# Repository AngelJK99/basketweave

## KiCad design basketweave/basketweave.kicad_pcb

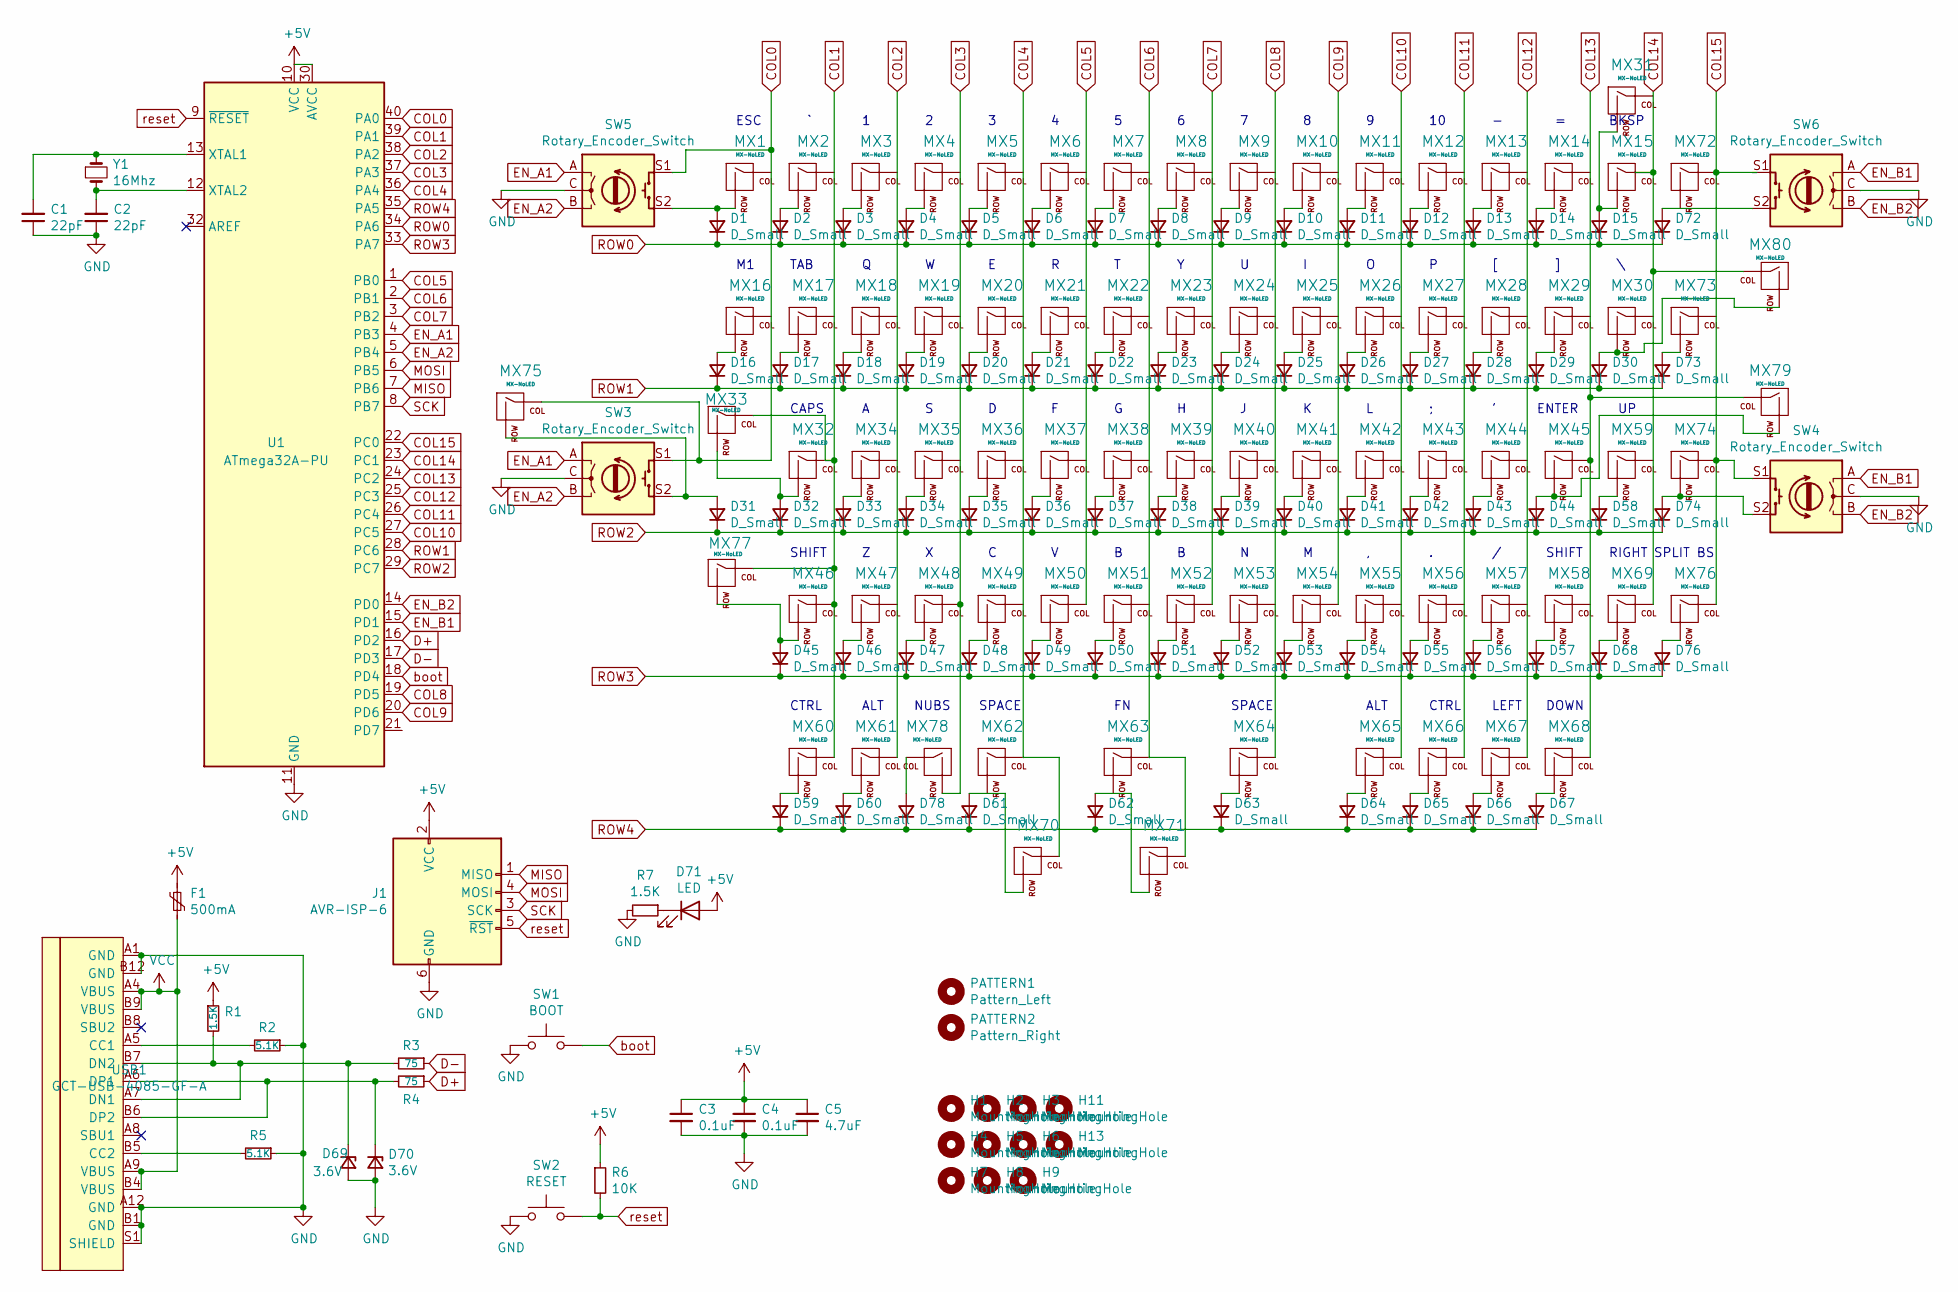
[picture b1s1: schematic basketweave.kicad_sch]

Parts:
C1, C2: 22pF; C_Disc_D3.0mm_W2.0mm_P2.50mm
C3, C4: 0.1uF; C_Disc_D4.3mm_W1.9mm_P5.00mm
C5: 4.7uF; CP_Radial_D4.0mm_P1.50mm
D1, D2, D3, D4, D5, D6, D7, D8, D9, D10, D11, D12, D13, D14, D15, D16, D17, D18, D19, D20, D21, D22, D23, D24, D25, D26, D27, D28, D29, D30, D31, D32, D33, D34, D35, D36, D37, D38, D39, D40, D41, D42, D43, D44, D45, D46, D47, D48, D49, D50, D51, D52, D53, D54, D55, D56, D57, D58, D59, D60, D61, D62, D63, D64, D65, D66, D67, D68, D72, D73, D74, D76, D78: D_Small; D_DO-35_SOD27_P7.62mm_Horizontal
D69, D70: 3.6V; D_DO-35_SOD27_P7.62mm_Horizontal
D71: LED; LED_D3.0mm_Clear
F1: 500mA; polyfuse_5.1mm
H1, H2, H3, H4, H5, H6, H7, H8, H9, H11, H13: MountingHole; MountingHole_2.2mm_M2_Pad
J1: AVR-ISP-6; PinHeader_2x03_P2.54mm_Vertical
MX1, MX2, MX3, MX4, MX5, MX6, MX7, MX8, MX9, MX10, MX11, MX12, MX13, MX14, MX16, MX18, MX19, MX20, MX21, MX22, MX23, MX24, MX25, MX26, MX27, MX28, MX29, MX31, MX34, MX35, MX36, MX37, MX38, MX39, MX40, MX41, MX42, MX43, MX44, MX47, MX48, MX49, MX50, MX51, MX52, MX53, MX54, MX55, MX56, MX57, MX59, MX67, MX68, MX69, MX71, MX72, MX73, MX74, MX75, MX76, MX78, MX80: MX-NoLED; MXOnly-1U-NoLED
MX15: MX-NoLED; MXOnly-2U-NoLED
MX17, MX30, MX60, MX61, MX65, MX66: MX-NoLED; MXOnly-1.5U-NoLED
MX32, MX63, MX77: MX-NoLED; MXOnly-1.25U-NoLED
MX33, MX58: MX-NoLED; MXOnly-1.75U-NoLED
MX45, MX46, MX70: MX-NoLED; MXOnly-2.25U-ReversedStabilizers-NoLED
MX62: MX-NoLED; MXOnly-2U-ReversedStabilizers-NoLED
MX64: MX-NoLED; MXOnly-2.75U-ReversedStabilizers-NoLED
MX79: MX-NoLED; MXOnly-ISO-ROTATED-ReversedStabilizers-NoLED
PATTERN1: Pattern_Left; pattern_left
PATTERN2: Pattern_Right; pattern_right
R1, R7: 1.5K; R_Axial_DIN0204_L3.6mm_D1.6mm_P5.08mm_Horizontal
R2, R5: 5.1K; R_Axial_DIN0204_L3.6mm_D1.6mm_P5.08mm_Horizontal
R3, R4: 75; R_Axial_DIN0204_L3.6mm_D1.6mm_P5.08mm_Horizontal
R6: 10K; R_Axial_DIN0204_L3.6mm_D1.6mm_P5.08mm_Horizontal
SW1: BOOT; SW_PUSH_6mm
SW2: RESET; SW_PUSH_6mm
SW3, SW4, SW5, SW6: Rotary_Encoder_Switch; RotaryEncoder_Alps_EC11E-Switch_Vertical_H20mm-for-MX
U1: ATmega32A-PU; DIP-40_W15.24mm
USB1: GCT-USB-4085-GF-A; USB_C_GCT_USB4085
Y1: 16Mhz; Crystal_HC49-4H_Vertical

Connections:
+5V: C3.1, C4.1, C5.1, D71.2 (A), F1.1, J1.2 (VCC), R1.1, R6.1, U1.10 (VCC), U1.30 (AVCC)
COL0: MX75.1 (COL), SW3.S1, SW5.S1, U1.40 (PA0)
COL1: MX32.1 (COL), MX33.1 (COL), MX46.1 (COL), MX60.1 (COL), MX77.1 (COL), U1.39 (PA1)
COL2: MX61.1 (COL), U1.38 (PA2)
COL3: MX48.1 (COL), MX78.2 (ROW), U1.37 (PA3)
COL4: MX62.1 (COL), MX70.1 (COL), U1.36 (PA4)
COL5: MX50.1 (COL), U1.1 (PB0)
COL6: MX63.1 (COL), MX71.1 (COL), U1.2 (PB1)
COL7: MX52.1 (COL), U1.3 (PB2)
COL8: MX64.1 (COL), U1.19 (PD5)
COL9: MX54.1 (COL), U1.20 (PD6)
COL10: MX65.1 (COL), U1.27 (PC5)
COL11: MX66.1 (COL), U1.26 (PC4)
COL12: MX67.1 (COL), U1.25 (PC3)
COL13: MX45.1 (COL), MX68.1 (COL), MX79.1 (COL), U1.24 (PC2)
COL14: MX15.1 (COL), MX69.1 (COL), MX80.1 (COL), U1.23 (PC1)
COL15: MX72.1 (COL), MX74.1 (COL), MX76.1 (COL), SW4.S1, U1.22 (PC0)
D+: R4.1, U1.16 (PD2)
D-: R3.1, U1.17 (PD3)
EN_A1: SW3.A, SW5.A, U1.4 (PB3)
EN_A2: SW3.B, SW5.B, U1.5 (PB4)
EN_B1: SW4.A, SW6.A, U1.15 (PD1)
EN_B2: SW4.B, SW6.B, U1.14 (PD0)
GND: C1.1, C2.1, C3.2, C4.2, C5.2, D69.2 (A), D70.2 (A), J1.6 (GND), R2.1, R5.1, R7.2, SW1.1, SW2.1, SW3.C, SW4.C, SW5.C, SW6.C, U1.11 (GND), U1.31 (GND), USB1.A1 (GND), USB1.A12 (GND), USB1.B1 (GND), USB1.B12 (GND), USB1.S1 (SHIELD)
MISO: J1.1 (MISO), U1.7 (PB6)
MOSI: J1.4 (MOSI), U1.6 (PB5)
unnamed: D1.2 (A), MX1.2 (ROW), SW5.S2
unnamed: D2.2 (A), MX2.2 (ROW)
unnamed: D3.2 (A), MX3.2 (ROW)
unnamed: D4.2 (A), MX4.2 (ROW)
unnamed: D5.2 (A), MX5.2 (ROW)
unnamed: D6.2 (A), MX6.2 (ROW)
unnamed: D7.2 (A), MX7.2 (ROW)
unnamed: D8.2 (A), MX8.2 (ROW)
unnamed: D9.2 (A), MX9.2 (ROW)
unnamed: D10.2 (A), MX10.2 (ROW)
unnamed: D11.2 (A), MX11.2 (ROW)
unnamed: D12.2 (A), MX12.2 (ROW)
unnamed: D13.2 (A), MX13.2 (ROW)
unnamed: D14.2 (A), MX14.2 (ROW)
unnamed: D15.2 (A), MX15.2 (ROW), MX31.2 (ROW)
unnamed: D16.2 (A), MX16.2 (ROW)
unnamed: D17.2 (A), MX17.2 (ROW)
unnamed: D18.2 (A), MX18.2 (ROW)
unnamed: D19.2 (A), MX19.2 (ROW)
unnamed: D20.2 (A), MX20.2 (ROW)
unnamed: D21.2 (A), MX21.2 (ROW)
unnamed: D22.2 (A), MX22.2 (ROW)
unnamed: D23.2 (A), MX23.2 (ROW)
unnamed: D24.2 (A), MX24.2 (ROW)
unnamed: D25.2 (A), MX25.2 (ROW)
unnamed: D26.2 (A), MX26.2 (ROW)
unnamed: D27.2 (A), MX27.2 (ROW)
unnamed: D28.2 (A), MX28.2 (ROW)
unnamed: D29.2 (A), MX29.2 (ROW)
unnamed: D30.2 (A), MX30.2 (ROW), MX80.2 (ROW)
unnamed: D31.2 (A), MX75.2 (ROW), SW3.S2
unnamed: D32.2 (A), MX32.2 (ROW), MX33.2 (ROW)
unnamed: D33.2 (A), MX34.2 (ROW)
unnamed: D34.2 (A), MX35.2 (ROW)
unnamed: D35.2 (A), MX36.2 (ROW)
unnamed: D36.2 (A), MX37.2 (ROW)
unnamed: D37.2 (A), MX38.2 (ROW)
unnamed: D38.2 (A), MX39.2 (ROW)
unnamed: D39.2 (A), MX40.2 (ROW)
unnamed: D40.2 (A), MX41.2 (ROW)
unnamed: D41.2 (A), MX42.2 (ROW)
unnamed: D42.2 (A), MX43.2 (ROW)
unnamed: D43.2 (A), MX44.2 (ROW)
unnamed: D44.2 (A), MX45.2 (ROW), MX79.2 (ROW)
unnamed: D45.2 (A), MX46.2 (ROW), MX77.2 (ROW)
unnamed: D46.2 (A), MX47.2 (ROW)
unnamed: D47.2 (A), MX48.2 (ROW)
unnamed: D48.2 (A), MX49.2 (ROW)
unnamed: D49.2 (A), MX50.2 (ROW)
unnamed: D50.2 (A), MX51.2 (ROW)
unnamed: D51.2 (A), MX52.2 (ROW)
unnamed: D52.2 (A), MX53.2 (ROW)
unnamed: D53.2 (A), MX54.2 (ROW)
unnamed: D54.2 (A), MX55.2 (ROW)
unnamed: D55.2 (A), MX56.2 (ROW)
unnamed: D56.2 (A), MX57.2 (ROW)
unnamed: D57.2 (A), MX58.2 (ROW)
unnamed: D58.2 (A), MX59.2 (ROW)
unnamed: D59.2 (A), MX60.2 (ROW)
unnamed: D60.2 (A), MX61.2 (ROW)
unnamed: D61.2 (A), MX70.2 (ROW)
unnamed: D62.2 (A), MX71.2 (ROW)
unnamed: D63.2 (A), MX64.2 (ROW)
unnamed: D64.2 (A), MX65.2 (ROW)
unnamed: D65.2 (A), MX66.2 (ROW)
unnamed: D66.2 (A), MX67.2 (ROW)
unnamed: D67.2 (A), MX68.2 (ROW)
unnamed: D68.2 (A), MX69.2 (ROW)
unnamed: D69.1 (K), R1.2, R3.2, USB1.A7 (DN1), USB1.B7 (DN2)
unnamed: D70.1 (K), R4.2, USB1.A6 (DP1), USB1.B6 (DP2)
unnamed: D71.1 (K), R7.1
unnamed: D72.2 (A), SW6.S2
unnamed: D73.2 (A), MX73.2 (ROW)
unnamed: D74.2 (A), MX74.2 (ROW), SW4.S2
unnamed: D76.2 (A), MX76.2 (ROW)
unnamed: D78.2 (A), MX78.1 (COL)
unnamed: C1.2, U1.13 (XTAL1), Y1.1
unnamed: C2.2, U1.12 (XTAL2), Y1.2
unnamed: R2.2, USB1.A5 (CC1)
unnamed: R5.2, USB1.B5 (CC2)
ROW0: D1.1 (K), D2.1 (K), D3.1 (K), D4.1 (K), D5.1 (K), D6.1 (K), D7.1 (K), D8.1 (K), D9.1 (K), D10.1 (K), D11.1 (K), D12.1 (K), D13.1 (K), D14.1 (K), D15.1 (K), D72.1 (K), U1.34 (PA6)
ROW1: D16.1 (K), D17.1 (K), D18.1 (K), D19.1 (K), D20.1 (K), D21.1 (K), D22.1 (K), D23.1 (K), D24.1 (K), D25.1 (K), D26.1 (K), D27.1 (K), D28.1 (K), D29.1 (K), D30.1 (K), D73.1 (K), U1.28 (PC6)
ROW2: D31.1 (K), D32.1 (K), D33.1 (K), D34.1 (K), D35.1 (K), D36.1 (K), D37.1 (K), D38.1 (K), D39.1 (K), D40.1 (K), D41.1 (K), D42.1 (K), D43.1 (K), D44.1 (K), D58.1 (K), D74.1 (K), U1.29 (PC7)
ROW3: D45.1 (K), D46.1 (K), D47.1 (K), D48.1 (K), D49.1 (K), D50.1 (K), D51.1 (K), D52.1 (K), D53.1 (K), D54.1 (K), D55.1 (K), D56.1 (K), D57.1 (K), D68.1 (K), D76.1 (K), U1.33 (PA7)
ROW4: D59.1 (K), D60.1 (K), D61.1 (K), D62.1 (K), D63.1 (K), D64.1 (K), D65.1 (K), D66.1 (K), D67.1 (K), D78.1 (K), U1.35 (PA5)
SCK: J1.3 (SCK), U1.8 (PB7)
VCC: F1.2, USB1.A4 (VBUS), USB1.A9 (VBUS), USB1.B4 (VBUS), USB1.B9 (VBUS)
boot: SW1.2, U1.18 (PD4)
reset: J1.5 (~RST), R6.2, SW2.2, U1.9 (~RESET)

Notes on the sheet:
ESC
NUBS
SPLIT BS
ALT
SPACE
CAPS
SHIFT
CTRL
TAB
DOWN
BKSP
ENTER
LEFT
RIGHT

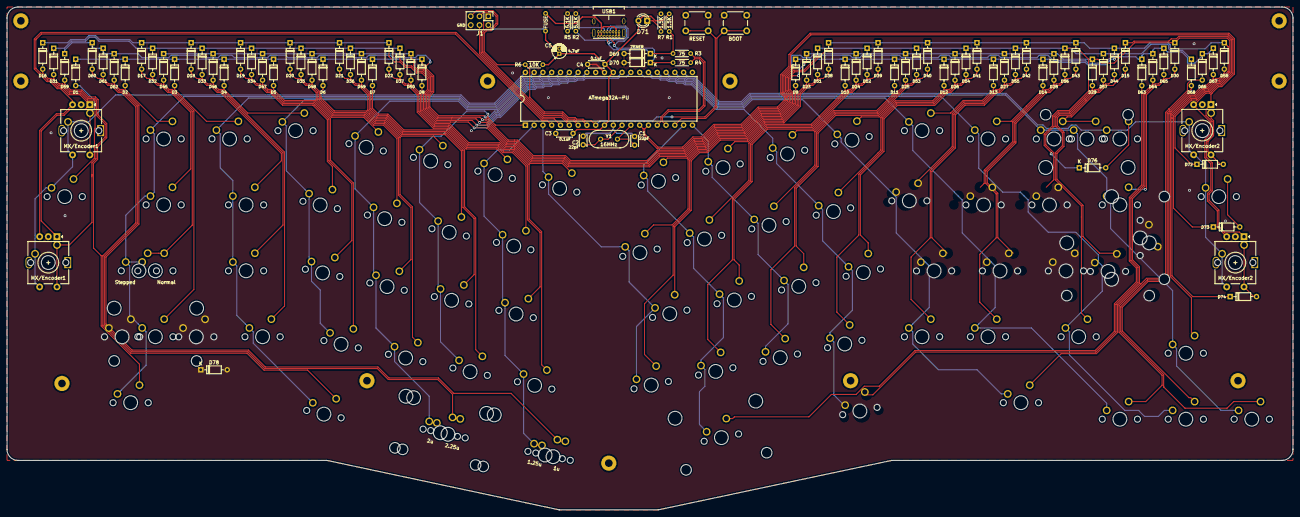
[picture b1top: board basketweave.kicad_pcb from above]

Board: 2 copper layers, 371.5 x 145.3 mm, 192 parts (0 on the bottom side), 115 nets.

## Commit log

2024-05-14 Working layout 14/05
